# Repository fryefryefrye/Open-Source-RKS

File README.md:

# Open-Source-RKS
### What is a RKS system
RKS as the Remote keyless system. It's a proximity system that is triggered if a key is within a certain distance. <br> 
Widely used in modern vehicles. It's very convenient to Entry your car when you have RKS system. <br> 
You do not need take out of your key, just walk to your car with the key in your pocket, then you can open the door.<br>

 <br>

<br> But do you want open the door of your home without take out your keys? Or equipment RKS to your old car?<br> 
I've found a solution that every electronic fans can make a RKS system at home in a very cheap price.<br> 
An iPhone without any app can be used as a wireless tag<br> 
Arduino based Controller can make you to use this system in any application if you like.<br>  
You can submit a issue or mail to me if you have any question.<br> 
<br>
## New update: Use your iPhone as a Tag.
### iPhone:
When IOS is enabling with continuity service, it will always sending BLE advertising to let other IOS device to know. But the Bluetooth MAC Address is random and changed every 15 minutes. <br>
With my another project, you can decode the random address and determined if this random address belongs to your phone.<br>
https://github.com/fryefryefrye/Decoding-Random-Bluetooth-Address/<br>
### Android:
Use "nRF Connect" APP, you can send BLE advertising with custom data.A name can be set in the advertising.<br>

## Hardware used:

iPhone; ESP32 Board; Arduino Board; nRF24L01 module

## Get IRK of your iPhone
If the IRK of an IOS device is known, the random Bluetooth address can be determined if it belongs to this device. <br>
### Use an ESP32 board and download with “iPhone/get_irk” project. It will start a BLE service. <br>
Pay attention on following settings.<br>
 <br>
### Use your iPhone install with “LightBlue” APP, find the “ESP_BLE_SECURITY” service, and connect it, the IRK will be print out. <br>
 <br>

## Receiver / Monitor BLE advertising with nRF24L01
With the help of the following project, we can Monitor BLE advertising with very cheap nRF24L01 module<br>
https://github.com/Pranavgulati/RF24BLE<br>
https://github.com/nRF24/RF24<br>
Install above two library into Arduino.<br>
Fill the IRK into the “iPhone/ReceiverController” project..<br>
Download “iPhone/ReceiverController” project into a Arduino nano board, you can Monitor BLE advertising and determine if the MAC address in the air is belong to your iPhone.<br><br>
These is only one key function you need to call to check MAC address. Everything needed for this function is in key.h file.You can use it in your other project.<br>
BOOLEAN btm_ble_addr_resolvable(BD_ADDR rpa, esp_bt_octet16_t irk)<br><br>

You can build the Arduino based BLE Monitor Just connect nRF24L01 module with Arduino follow the table.<br>

 <br>

 <br>

When you are OK to this stage, if you are walking to your reciver with your iPhone, the arduino will know you are coming.<br>
And you can write your applaction code. Like close a relay to open a door.<br>

## Old version: Released on 2016. Use Independent Wireless Tag.

### A very simple wireless Key. 

nRF24LE1 module and CR2032 battery are the only thing to make a key for RKS system. <br>
nRF24LE1 is Ultra-low Power Wireless System On-Chip Solution.<br>
An 8051 compatible MCU is attached in it. So one chip is enough.<br>

### Arduino based Controller

An Arduino equipment with a nRF24L01 module, can receive the data from the key nearby.<br> 
Arduino based Controller is very easy to program, and you can make any application if you wish base on this RKS system.<br> 
In This example, a relay will be used as the output. <br> 
When key goes close in about 2 meters, the relay closed.<br> 
When key goes far away, the relay will be disconnect.<br> 
.

### How they made?
* Make the Tag/Key/Transmitter

First you need program the nRF24LE1 use a Programmer.<br>
After that, just connect 2 cables from battery to power on the nRF24LE1 module is OK.<br>
All the needles on the module can be cut to short to fit in the thin case.<br>

.<br>

* Make the Controller/Receiver

You can build the Arduino based Controller whatever you like. Just connect nRF24L01 module with Arduino follow the table.<br>

| PIN  | NRF24L01|Arduino UNO/NANO|Mega1280/2560|
| ---------- | -----------| -----------| -----------|
|  1  |  GND  |  GND  |  GND  |
|  2  |  VCC  |  3.3V  |  3.3V  |
|  3  |  CE   |  digIO 7  |  digIO 7  |
|  4  |  CSN  |  digIO 8  |  digIO 8  |
|  5  |  SCK   |  digIO 13  |  digIO 52  |
|  6  |  MOSI  |  digIO 11  |  digIO 51  |
|  7  |  MISO  | digIO 12  |  digIO 50  |
|  8  |  IRQ  |  -  |-|
<br> 

<br>
This is combination I used in debug stage.<br> 

<br> 

<br>
The PCB for Controller is on the way, I will update soon.<br>

## Technical details

### Frequency hopping

The key, as an Active RFID Tag, will transmit its ID and the volt of the battery 3 times every second in 3 different channels.<br> 
The Controller, as the receiver, will listening on these 3 different channels, one channel for one second.<br> 
This will make the system more anti-interference.<br> 

### Power Consumption of the Tag

<br> 

The above picture is Current sampling with a 47 Ohm resistor.<br> 

For every time of transmit. Power consumption can be estimated as:  <br> 
0.7v\*47Ohm = 32.9mA<br> 
Duration for 0.3ms <br> <br> 
Capacity of a CR2032 battery is 200 mAh.<br> 
In This example, data was transmit 3 times in every second. <br> 
Estimated life days = (200/(32.9\*(0.0003/3600)))/3/3600/24 = 281 days <br> 

## Hardware used in this project

* Tag/Key/Transmitter

### nRF24LE1 module
Reference price € 4.00<br> 
<br> 

### Programmer for nRF24LE1
Reference price € 15.00<br> 
<br> 

### nRF24LE1 adapter.
Reference price € 5.00<br> 
<br> 

### CR2032 battery
Reference price € 1.00<br> 
<br> 

### Plastic case of the key
Reference price € 1.00<br> 
<br> 

### PCB of the key
Reference price € 1.00<br> 
Send the file PCB\Files_for_Factory_made\tag.cam to PCB factory, they can make it for you.<br> 
A programmer interface is placed on the PCB, you can also program the nRF24LE1 with this port after the module have been soldered on the PCB.<br> 
Or you can use any method you can do to connect the module with battery.<br> 
<br> 

### Battery holder in the key
Reference price € 1.00<br> 
<br> 

* Controller/Receiver

### Arduino
Reference price € 5.00<br> 
<br> 

### nRF24L01 module
Reference price € 2.00<br> 
<br> 

### Integrated PCB of Controller
Reference price € 2.00<br> 
<br> 

### Buzz module
Reference price € 1.00<br> 
<br> 

### Relay module
Reference price € 1.00<br> 
<br> 

### nRF24L01+PA module
Reference price € 4.00<br> 
A more powerful nRF24L01+PA module can get longer range and has External antenna interface. It has a compatible interface with nRF24L01 module<br> 
But it need more power on 3.3v, so a AMS1117-3.3v can be used to power this module.<br> 
<br> 

### DC-DC Converter
Reference price € 1.00<br> 
Most of cars, door locking system are using 12v. So a DC-DC Converter is needed here to power the Arduino with 5v. <br>
<br> 

## Video

## Draft

After check the ID of the key, it will drive the relay to Unlock the door for you.<br> 
When the key is get a little far away, the relay will release and the door will be locked.<br> 
You can also equipment with some power system to open the door automatically.<br>

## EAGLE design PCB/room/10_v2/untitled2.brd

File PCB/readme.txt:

PCB was made by EAGLE-7.6.0.
Files in following foler can be send to Factory to make the PCB.
\PCB\Files_for_Factory_made

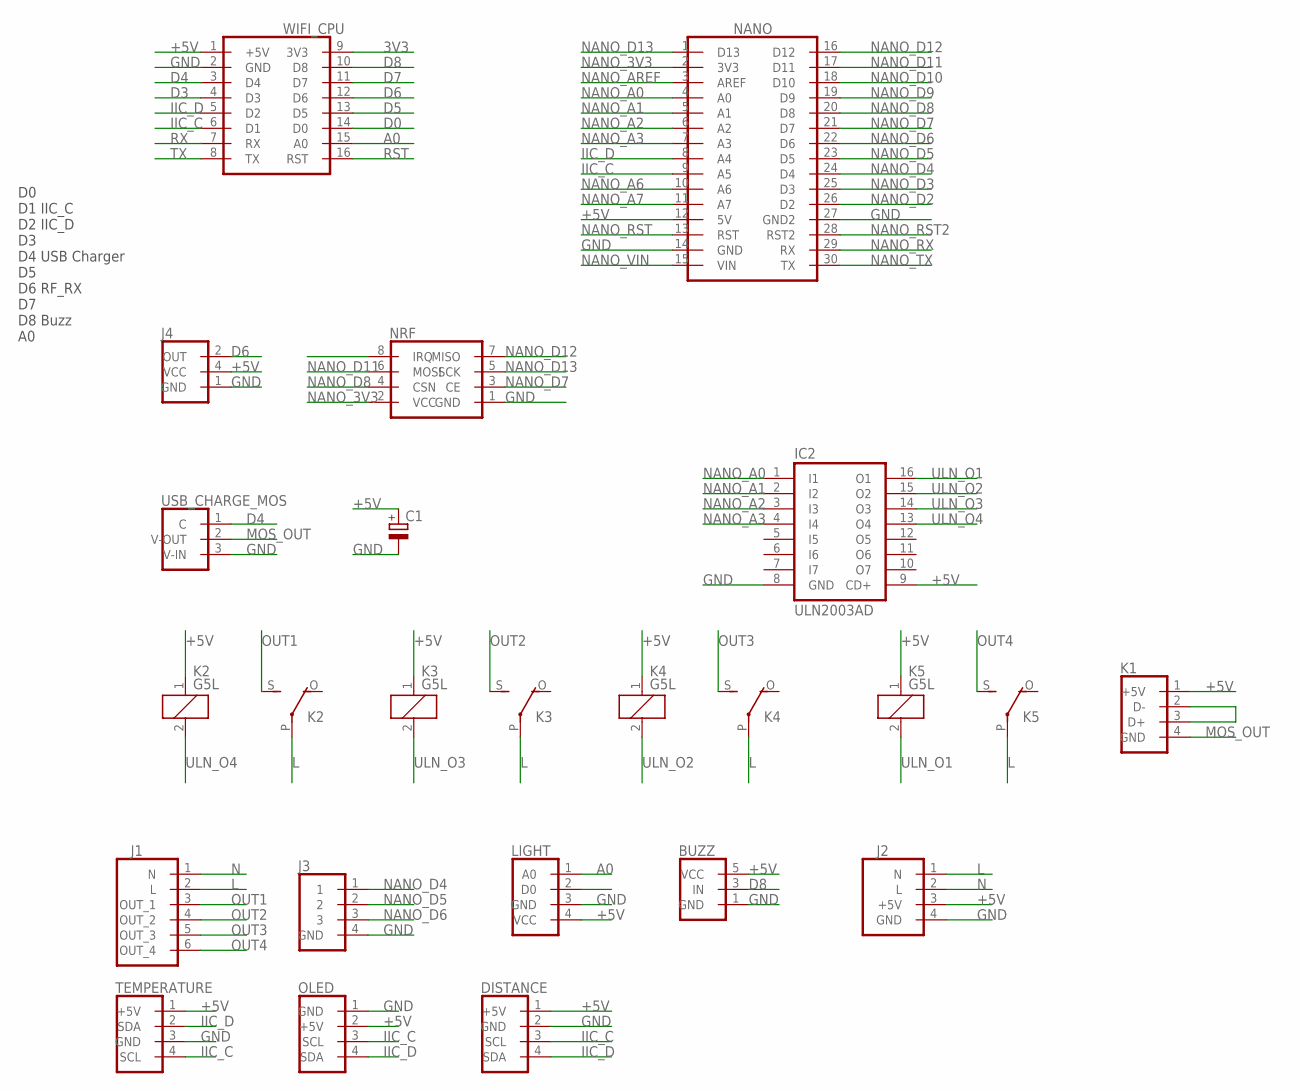
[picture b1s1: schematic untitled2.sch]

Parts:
BUZZ: BUZZ_MODULE
C1: CPOL-EUE5-5; E5-5
DISTANCE: IIC_DISTANCE
IC2: ULN2003AD; SO16
J1: OUT_HEAD_6_AC_4CH
J2: AC_DCSIDE_2A; AC_DC_SIDE_2A
J3: SELECT_1_IN_3
J4: 315MHZ_RX_SMT_LONG
K1: USB_OUTUSB_V; USB_V_OUT
K2, K3, K4, K5: G5L; G5LE
LIGHT: LIGHT_DEC
NANO: ARDUINO_NANO
NRF: NRF24L01_MODULE; NRF24L01
OLED: IIC_OLED
TEMPERATURE: IIC_TEMPERATURE
USB_CHARGE_MOS: MOS_IRF520
WIFI_CPU: ESP8266_MINI

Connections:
3V3: WIFI_CPU.9 (3V3)
+5V: BUZZ.5 (VCC), C1.+, DISTANCE.1 (+5V), IC2.9 (CD+), J2.3 (+5V), J4.4 (VCC), K1.1 (+5V), K2.1, K3.1, K4.1, K5.1, LIGHT.4 (VCC), NANO.12 (5V), OLED.2 (+5V), TEMPERATURE.1 (+5V), WIFI_CPU.1 (+5V)
A0: LIGHT.1 (A0), WIFI_CPU.15 (A0)
D0: WIFI_CPU.14 (D0)
D3: WIFI_CPU.4 (D3)
D4: USB_CHARGE_MOS.1 (C), WIFI_CPU.3 (D4)
D5: WIFI_CPU.13 (D5)
D6: J4.2 (OUT), WIFI_CPU.12 (D6)
D7: WIFI_CPU.11 (D7)
D8: BUZZ.3 (IN), WIFI_CPU.10 (D8)
GND: BUZZ.1 (GND), C1.-, DISTANCE.2 (GND), IC2.8 (GND), J2.4 (GND), J3.4 (GND), J4.1 (GND), LIGHT.3 (GND), NANO.14 (GND), NANO.27 (GND2), NRF.1 (GND), OLED.1 (GND), TEMPERATURE.3 (GND), USB_CHARGE_MOS.3 (V-IN), WIFI_CPU.2 (GND)
IIC_C: DISTANCE.3 (SCL), NANO.9 (A5), OLED.3 (SCL), TEMPERATURE.4 (SCL), WIFI_CPU.6 (D1)
IIC_D: DISTANCE.4 (SDA), NANO.8 (A4), OLED.4 (SDA), TEMPERATURE.2 (SDA), WIFI_CPU.5 (D2)
L: J1.2 (L), J2.1 (N), K2.P, K3.P, K4.P, K5.P
MOS_OUT: K1.4 (GND), USB_CHARGE_MOS.2 (V-OUT)
N: J1.1 (N), J2.2 (L)
unnamed: K1.2 (D-), K1.3 (D+)
NANO_3V3: NANO.2 (3V3), NRF.2 (VCC)
NANO_A0: IC2.1 (I1), NANO.4 (A0)
NANO_A1: IC2.2 (I2), NANO.5 (A1)
NANO_A2: IC2.3 (I3), NANO.6 (A2)
NANO_A3: IC2.4 (I4), NANO.7 (A3)
NANO_A6: NANO.10 (A6)
NANO_A7: NANO.11 (A7)
NANO_AREF: NANO.3 (AREF)
NANO_D2: NANO.26 (D2)
NANO_D3: NANO.25 (D3)
NANO_D4: J3.1, NANO.24 (D4)
NANO_D5: J3.2, NANO.23 (D5)
NANO_D6: J3.3, NANO.22 (D6)
NANO_D7: NANO.21 (D7), NRF.3 (CE)
NANO_D8: NANO.20 (D8), NRF.4 (CSN)
NANO_D9: NANO.19 (D9)
NANO_D10: NANO.18 (D10)
NANO_D11: NANO.17 (D11), NRF.6 (MOSI)
NANO_D12: NANO.16 (D12), NRF.7 (MISO)
NANO_D13: NANO.1 (D13), NRF.5 (SCK)
NANO_RST: NANO.13 (RST)
NANO_RST2: NANO.28 (RST2)
NANO_RX: NANO.29 (RX)
NANO_TX: NANO.30 (TX)
NANO_VIN: NANO.15 (VIN)
OUT1: J1.3 (OUT_1), K2.S
OUT2: J1.4 (OUT_2), K3.S
OUT3: J1.5 (OUT_3), K4.S
OUT4: J1.6 (OUT_4), K5.S
RST: WIFI_CPU.16 (RST)
RX: WIFI_CPU.7 (RX)
TX: WIFI_CPU.8 (TX)
ULN_O1: IC2.16 (O1), K5.2
ULN_O2: IC2.15 (O2), K4.2
ULN_O3: IC2.14 (O3), K3.2
ULN_O4: IC2.13 (O4), K2.2

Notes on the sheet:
D0 D1 IIC_C D2 IIC_D D3 D4 USB Charger D5 D6 RF_RX D7 D8 Buzz A0

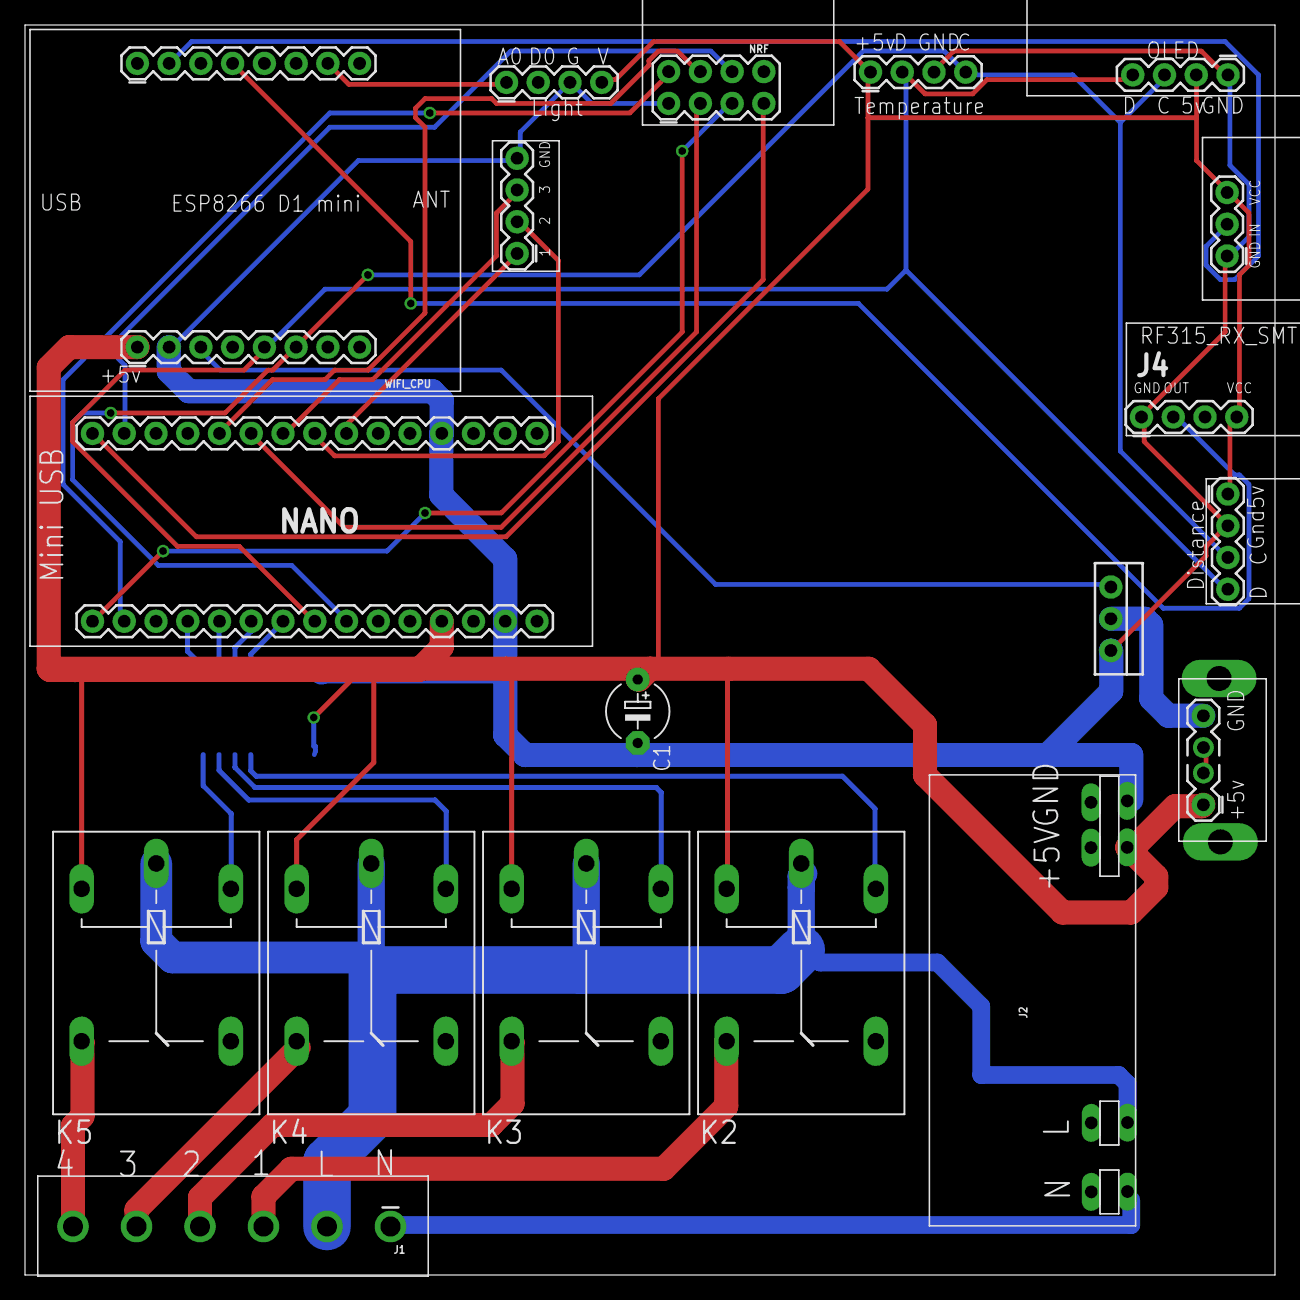
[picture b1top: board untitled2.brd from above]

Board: 2 copper layers, 100.0 x 100.0 mm, 20 parts (1 on the bottom side), 33 nets.

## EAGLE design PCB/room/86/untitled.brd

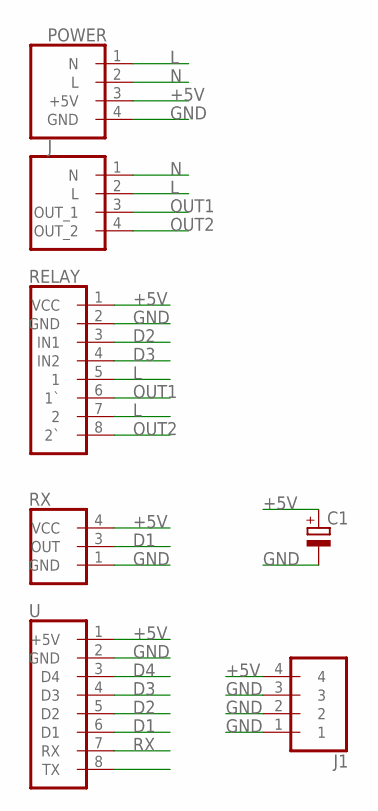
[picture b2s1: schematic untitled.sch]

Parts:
C1: CPOL-EUE5-5; E5-5
J: OUT_HEAD_4_AC_2CH
J1: 2.544; 2.54*4
POWER: AC_DC; AC_DC_SIDE
RELAY: 2_SOLID_RELAY
RX: 315MHZ_RX_UART
U: ESP8266_MINI_SIDE

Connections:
+5V: C1.+, J1.4, POWER.3 (+5V), RELAY.1 (VCC), RX.4 (VCC), U.1 (+5V)
D1: RX.3 (OUT), U.6 (D1)
D2: RELAY.3 (IN1), U.5 (D2)
D3: RELAY.4 (IN2), U.4 (D3)
D4: U.3 (D4)
GND: C1.-, J1.1, J1.2, J1.3, POWER.4 (GND), RELAY.2 (GND), RX.1 (GND), U.2 (GND)
L: J.2 (L), POWER.1 (N), RELAY.5 (1), RELAY.7 (2)
N: J.1 (N), POWER.2 (L)
OUT1: J.3 (OUT_1), RELAY.6 (1`)
OUT2: J.4 (OUT_2), RELAY.8 (2`)
RX: U.7 (RX)

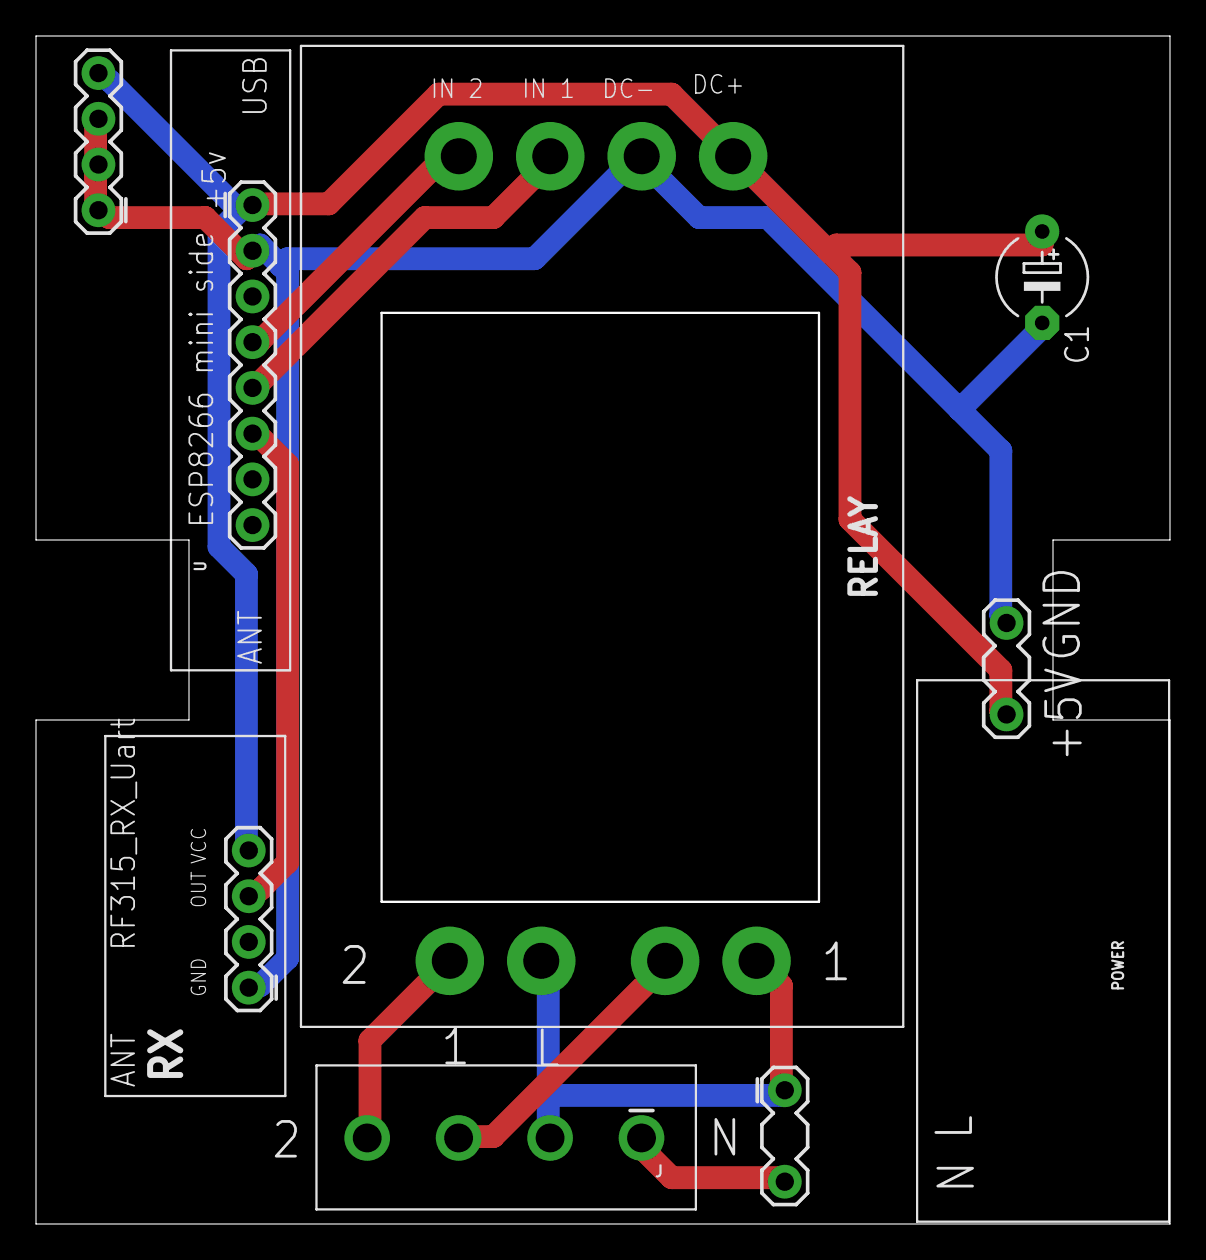
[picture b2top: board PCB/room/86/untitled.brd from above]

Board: 2 copper layers, 63.0 x 66.0 mm, 7 parts (0 on the bottom side), 9 nets.

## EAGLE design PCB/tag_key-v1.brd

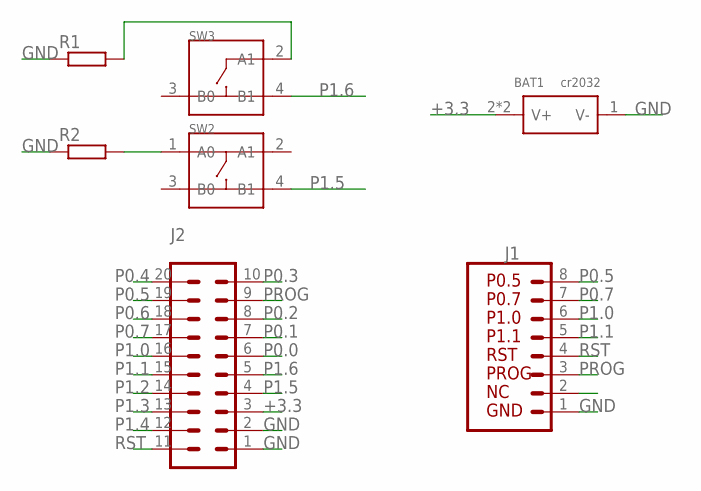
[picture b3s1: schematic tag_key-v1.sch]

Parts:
BAT1: cr2032; SEEED-OPL-CONNECTOR_BAT2P-20.32-CR2032
J1: SPARKFUN-CONNECTORS_CONN_08"; SPARKFUN-CONNECTORS_1X08
J2: SPARKFUN-CONNECTORS_CONN_11_1.27MM; SPARKFUN-CONNECTORS_1X11-1.27MM
R1, R2: RESISTOR_R-EU_M0805; RESISTOR_M0805
SW2: SEEED-OPL-SWITCH_SMD-BUTTON(4P-6.0X6.0X7.5MM); SEEED-OPL-SWITCH_SW4-SMD-4.5-6.0X6.0X7.5MM
SW3: SEEED-OPL-SWITCH_SMD-BUTTON(4P-6.0X6.0X3LEGM); SEEED-OPL-SWITCH_SW4-SMD-4.5-6.0X6.0_3LEG

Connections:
+3.3: BAT1.2 (V+), BAT1.3 (V+), J2.3
GND: BAT1.1 (V-), J1.1, J2.1, J2.2, R1.1, R2.1
unnamed: R2.2, SW2.1 (A0)
unnamed: R1.2, SW3.2 (A1)
P0.0: J2.6
P0.1: J2.7
P0.2: J2.8
P0.3: J2.10
P0.4: J2.20 (11)
P0.5: J1.8, J2.19 (12)
P0.6: J2.18 (13)
P0.7: J1.7, J2.17 (14)
P1.0: J1.6, J2.16 (15)
P1.1: J1.5, J2.15 (16)
P1.2: J2.14 (17)
P1.3: J2.13 (18)
P1.4: J2.12 (19)
P1.5: J2.4, SW2.4 (B1)
P1.6: J2.5, SW3.4 (B1)
PROG: J1.3, J2.9
RST: J1.4, J2.11 (20)

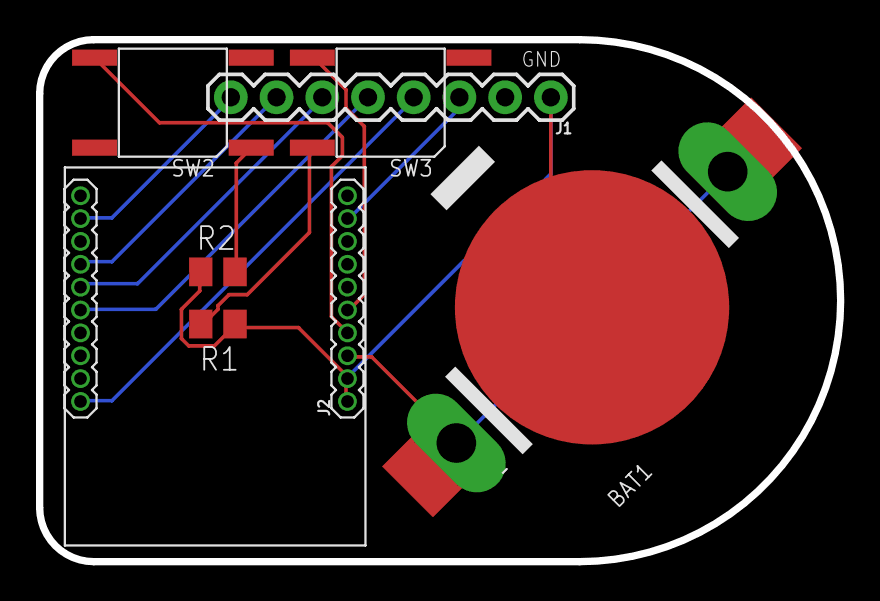
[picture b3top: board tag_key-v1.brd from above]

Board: 2 copper layers, 44.5 x 29.0 mm, 7 parts (0 on the bottom side), 12 nets.

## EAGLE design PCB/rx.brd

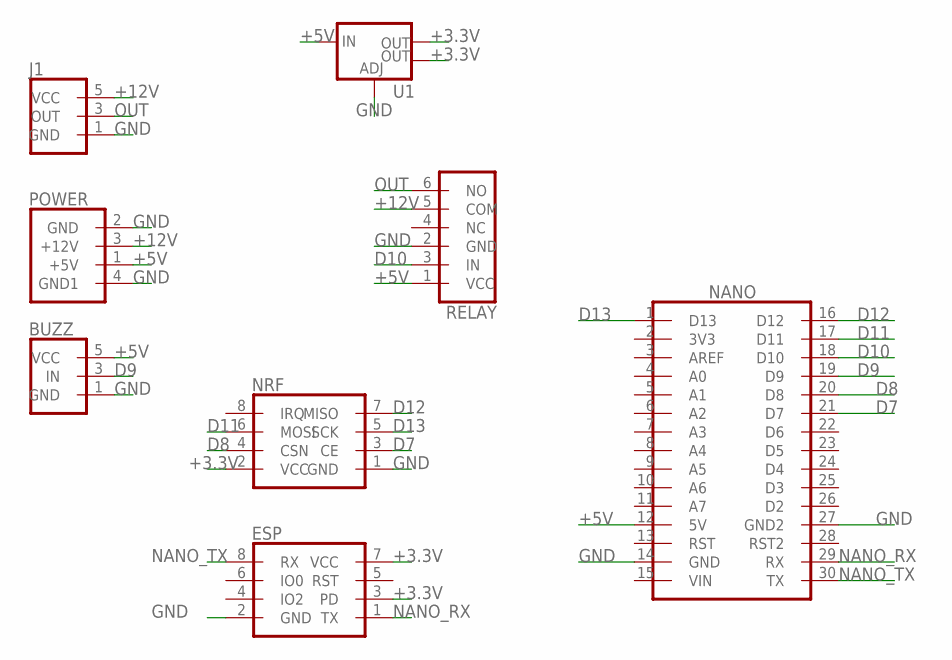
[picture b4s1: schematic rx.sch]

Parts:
BUZZ: BUZZ_MODULE
ESP: ESP8266_MODULE; ESP8266
J1: OUT_HEAD_3BIG; OUT_HEAD_3_BIG
NANO: ARDUINO_NANO
NRF: NRF24L01_MODULE_PA; NRF24L01_PA
POWER: POWER_REDUCE
RELAY: RELAY_MODULE
U1: V_REG_LM1117SOT223; SOT223

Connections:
+3.3V: ESP.3 (PD), ESP.7 (VCC), NRF.2 (VCC), U1.2 (OUT), U1.4 (OUT)
+5V: BUZZ.5 (VCC), NANO.12 (5V), POWER.1 (+5V), RELAY.1 (VCC), U1.3 (IN)
+12V: J1.5 (VCC), POWER.3 (+12V), RELAY.5 (COM)
D7: NANO.21 (D7), NRF.3 (CE)
D8: NANO.20 (D8), NRF.4 (CSN)
D9: BUZZ.3 (IN), NANO.19 (D9)
D10: NANO.18 (D10), RELAY.3 (IN)
D11: NANO.17 (D11), NRF.6 (MOSI)
D12: NANO.16 (D12), NRF.7 (MISO)
D13: NANO.1 (D13), NRF.5 (SCK)
GND: BUZZ.1 (GND), ESP.2 (GND), J1.1 (GND), NANO.14 (GND), NANO.27 (GND2), NRF.1 (GND), POWER.2 (GND), POWER.4 (GND1), RELAY.2 (GND), U1.1 (ADJ)
NANO_RX: ESP.1 (TX), NANO.29 (RX)
NANO_TX: ESP.8 (RX), NANO.30 (TX)
OUT: J1.3 (OUT), RELAY.6 (NO)

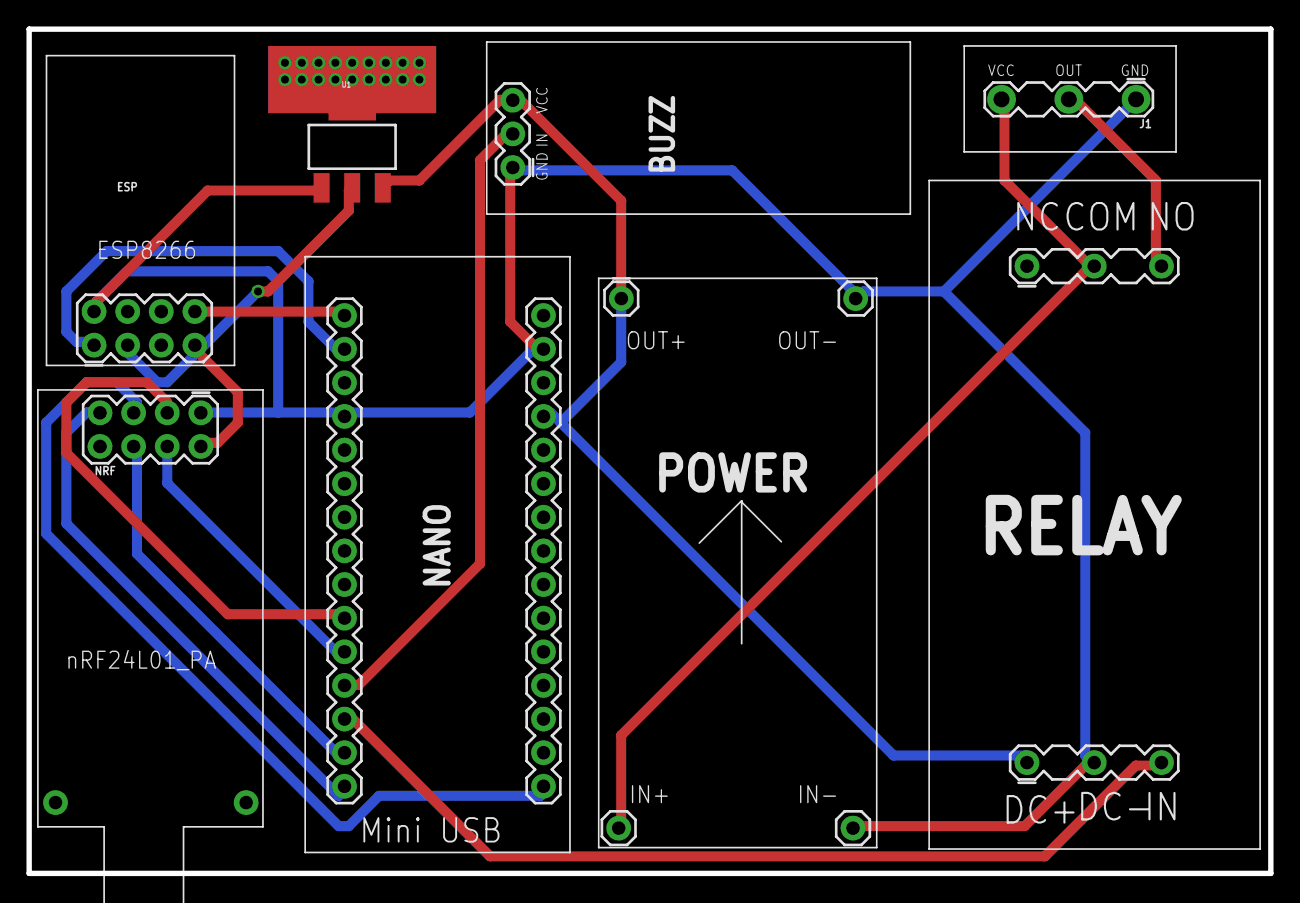
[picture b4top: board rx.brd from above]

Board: 2 copper layers, 93.8 x 63.8 mm, 8 parts (0 on the bottom side), 14 nets.

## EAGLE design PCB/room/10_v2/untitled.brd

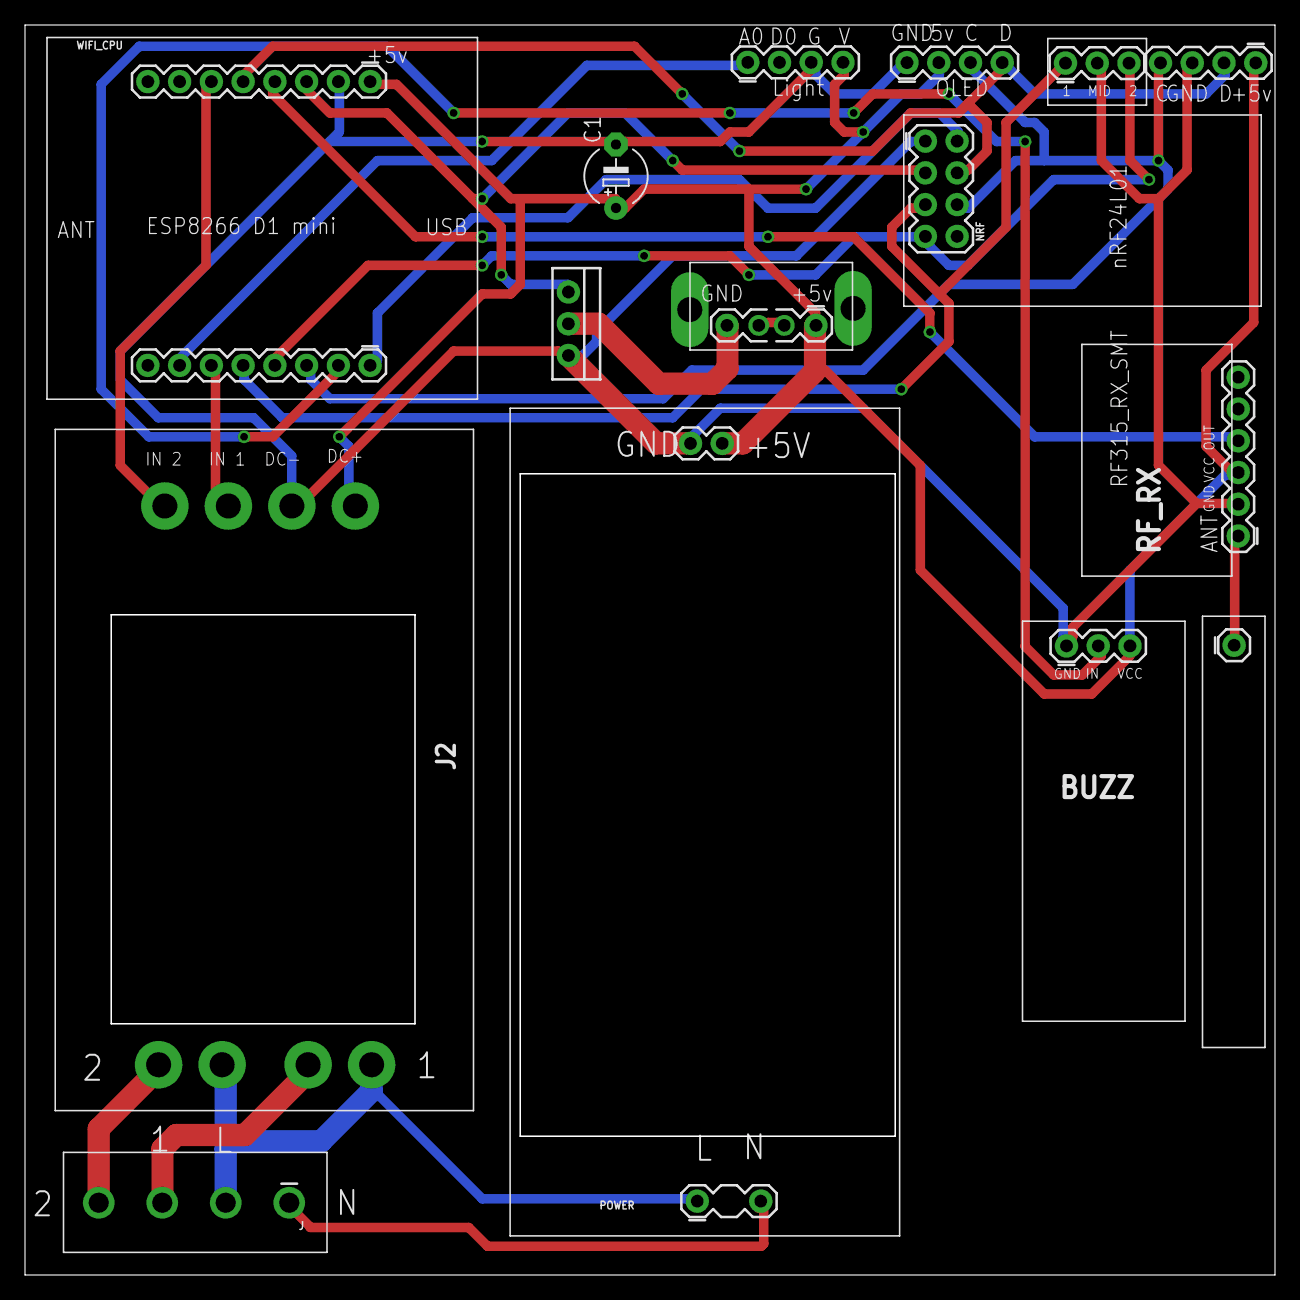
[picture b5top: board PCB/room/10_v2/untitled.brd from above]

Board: 2 copper layers, 100.0 x 100.0 mm, 15 parts (0 on the bottom side), 20 nets.

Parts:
BUZZ: BUZZ_MODULE
C1: E5-5
J: OUT_HEAD_4_AC_2CH
J2: 2_SOLID_RELAY
J3: ANT_315
K1: USB_V_OUT
LIGHT: LIGHT_DEC
LOCAL: SELECT_3
NRF: NRF24L01
OLED: IIC_OLED
POWER: AC_DC_5V2A
RF_RX: 315MHZ_RX_SMT
TEMPERATURE: IIC_TEMPERATURE
USB_CHARGE_MOS: MOS_IRF520
WIFI_CPU: ESP8266_MINI

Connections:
3V3: NRF.2, WIFI_CPU.9
+5V: BUZZ.5, C1.+, J2.1, K1.1, LIGHT.4, OLED.2, POWER.4, RF_RX.3, TEMPERATURE.1, WIFI_CPU.1
A0: LIGHT.1, WIFI_CPU.15
ANT: J3.1, RF_RX.1
D0: J2.3, WIFI_CPU.14
D1: J2.4, WIFI_CPU.6
D2: NRF.4, OLED.4, TEMPERATURE.2, WIFI_CPU.5
D3: RF_RX.4, WIFI_CPU.4
D4: NRF.3, USB_CHARGE_MOS.1, WIFI_CPU.3
D5: LOCAL.1, NRF.5, WIFI_CPU.13
D6: LOCAL.3, NRF.7, WIFI_CPU.12
D7: NRF.6, OLED.3, TEMPERATURE.4, WIFI_CPU.11
D8: BUZZ.3, WIFI_CPU.10
GND: BUZZ.1, C1.-, J2.2, LIGHT.3, LOCAL.2, NRF.1, OLED.1, POWER.3, RF_RX.2, TEMPERATURE.3, USB_CHARGE_MOS.3, WIFI_CPU.2
L: J.2, J2.5, J2.7, POWER.1
MOS_OUT: K1.4, USB_CHARGE_MOS.2
N: J.1, POWER.2
unnamed: K1.2, K1.3
OUT1: J.3, J2.6
OUT2: J.4, J2.8

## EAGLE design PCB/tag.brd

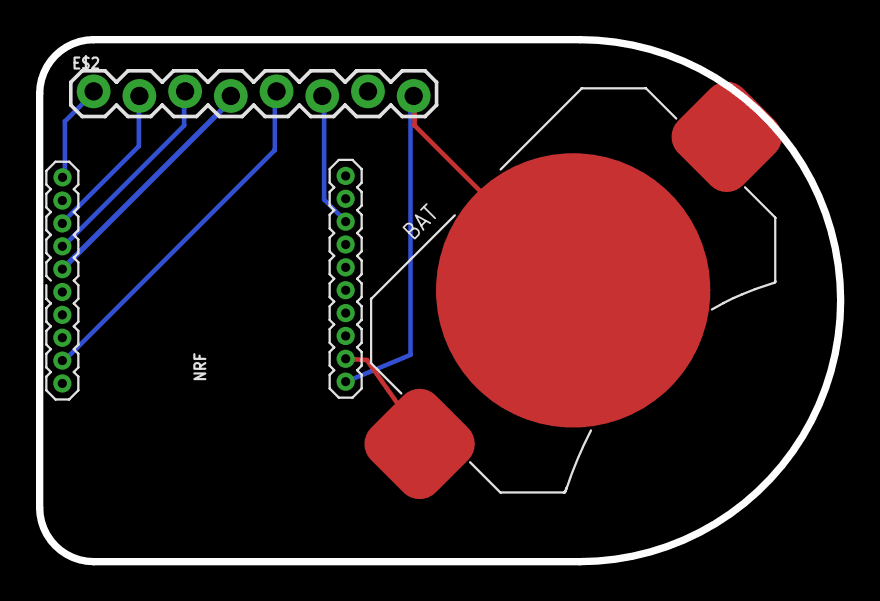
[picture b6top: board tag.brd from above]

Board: 2 copper layers, 44.5 x 29.0 mm, 3 parts (0 on the bottom side), 8 nets.

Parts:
BAT: BAT2P-SMD-20.32-CR2032
E$2: 1X08_LOCK
NRF: 1X11-1.27MM

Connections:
S$1: BAT.V-, E$2.8, NRF.1
S$2: BAT.V1, NRF.2
S$3: E$2.4, NRF.14
S$5: E$2.3, NRF.16
S$8: E$2.6, NRF.8
S$12: E$2.5, NRF.19
S$14: E$2.2, NRF.18
S$15: E$2.1, NRF.11

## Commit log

2017-08-03 add files
2017-08-04 update doc
2017-08-04 update doc and img
2017-08-04 doc update
2017-08-04 add power cal
2017-08-05 rename
2017-08-05 name
2017-08-05 dcdc
2017-08-05 3.3v for PA
2017-08-07 add 315mhz
2017-08-08 mini web
2017-08-08 add record
2017-08-09 pke img
2017-08-09 web prepare
2017-08-12 pcb_out,arduino struct
2017-08-13 Refactoring
2017-08-15 web update
2017-08-16 reset
2017-08-20 v1.0
2017-08-23 mail
2017-08-28 mail time out
2017-09-03 tag with key
2017-09-07 tag,mail
2017-09-19 new bike
2017-09-20 keypress
2017-09-26 time and time out
2017-09-26 fix no response
2017-09-26 timeout
2017-09-26 lock time
2017-09-27 keypress and timeout
2017-09-28 time to 30s
2017-10-14 alarm
2017-10-18 315 time
2017-12-01 time_ntp
2017-12-03 time out of get value
2017-12-08 submit for clock_GB
2017-12-16 qq smtp
2017-12-23 ava_data
2018-03-07 package div
2018-04-05 rc toy and power monitor
2018-04-22 315 command miss;charge mode amp
2018-05-29 pic of time
2018-05-30 Lock! exit park without key
2018-06-10 OLED lib move in
2018-06-10 weight is get
2018-06-11 weight v1.0
2018-06-24 sliding door
2018-08-21 weight update
2018-08-21 stru change
2018-08-21 ssl for clock
2018-09-08 PM_midpoint_modify
2018-10-07 alarm_charge
2018-11-13 ac control
2019-01-01 room_pcb,android
2019-01-20 auto_door
2019-03-08 meter
2019-03-09 pay_notice
2019-03-13 gprs doc
2019-03-16 led_time_gprs
2019-04-08 compressor_dect
2019-06-19 small_ac
2019-06-22 ac in small and canteen
2019-09-01 rf_esp
2019-10-15 taobao
2019-11-07 room10,pad_on_off
2019-11-17 esp32_ble
2019-11-21 rf24_BLE
2019-11-26 backup
2020-02-03 android udp tx rx
2020-02-29 led unit
2020-03-11 commit from 2019
2020-03-11 commit from vs2019
2020-03-12 led unit use u8g2
2020-03-17 sliding door distance
2020-03-22 PowerBank-PD
2020-03-23 LED_Unit CleanUp
2020-03-25 house keeping
2020-03-25 PowerBankPD-CleanUp
2020-04-22 rf_rx_oled
2020-05-07 room10_dual_cpu
2020-05-14 clear
2021-02-26 weather
2021-03-17 update home auto

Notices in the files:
parts and their libraries:
SparkFun-Connectors-10-1.27: Licensing: Creative Commons ShareAlike 4.0 International - https://creativecommons.org/licenses/by-sa/4.0
